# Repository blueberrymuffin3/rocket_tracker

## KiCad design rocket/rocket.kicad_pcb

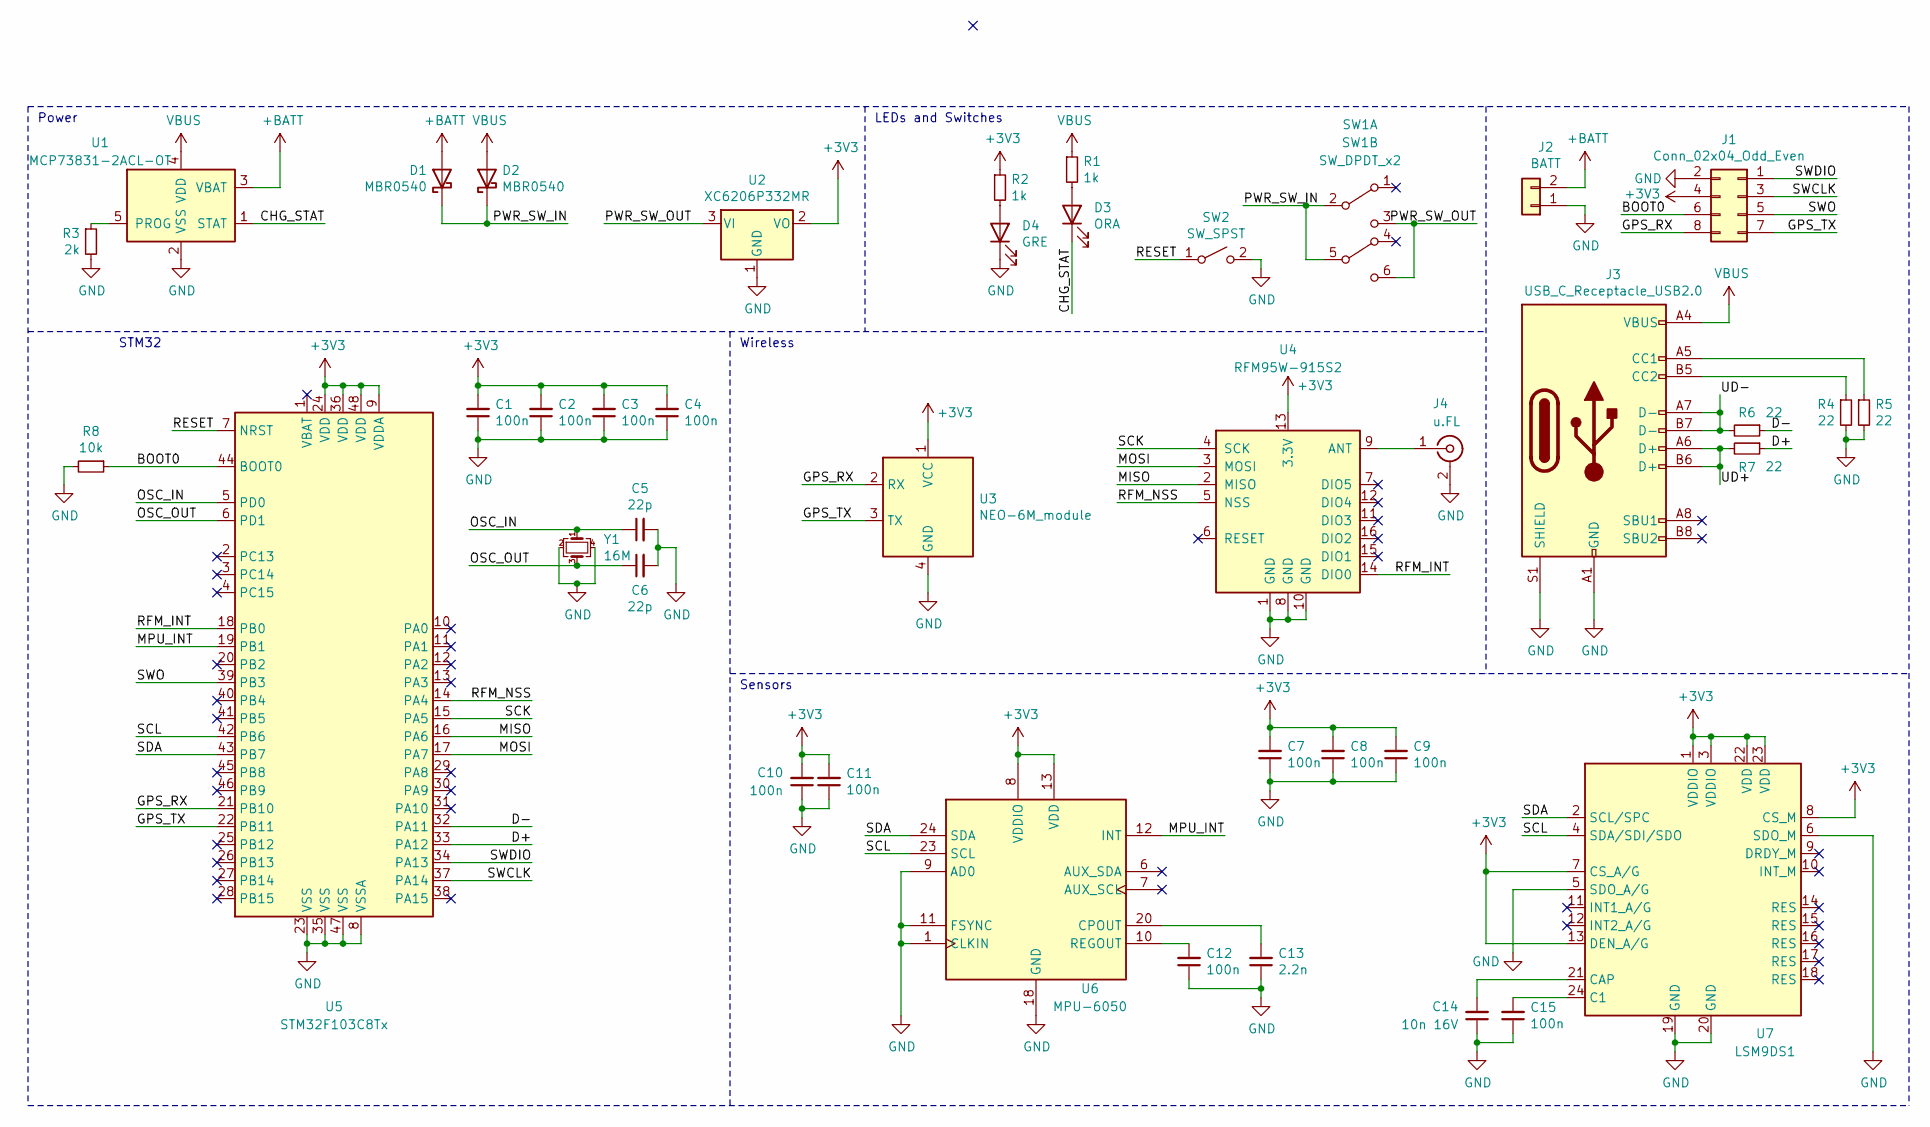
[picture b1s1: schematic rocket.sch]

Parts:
C1, C2, C3, C4, C7, C8, C9, C10, C11, C12, C15: 100n; C_0402_1005Metric; JLCPCB # C1525
C5, C6: 22p; C_0402_1005Metric; JLCPCB # C1555
C13: 2.2n; C_0402_1005Metric; JLCPCB # C1531
C14: 10n 16V; C_0402_1005Metric; JLCPCB # C15195
D1, D2: MBR0540; D_SOD-123; DIGIKEY # MBR0540TPMSCT-ND
D3: ORA; LED_0603_1608Metric; DIGIKEY # 160-1445-1-ND
D4: GRE; LED_0603_1608Metric; DIGIKEY # 160-1446-1-ND
J1: Conn_02x04_Odd_Even; PinSocket_2x04_P1.27mm_Horizontal_Straddle; DIGIKEY # 609-3753-ND, 609-3753-ND, 2057-RS1-04-G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
J2: BATT; JST_PH_S2B-PH-SM4-TB_1x02-1MP_P2.00mm_Horizontal; DIGIKEY # 455-1749-1-ND
J3: USB_C_Receptacle_USB2.0; GCT_USB4110-GF-A; DIGIKEY # 2073-USB4110-GF-A-1-ND
J4: u.FL; U.FL_Molex_MCRF_73412-0110_Vertical; DIGIKEY # A118077CT-ND
R1, R2: 1k; R_0402_1005Metric; JLCPCB # C11702
R3: 2k; R_0402_1005Metric; JLCPCB # C4109
R4, R5, R6, R7: 22; R_0402_1005Metric; JLCPCB # C25092
R8: 10k; R_0402_1005Metric; JLCPCB # C25744
SW1: SW_DPDT_x2; SW_DPDT_CK_JS202011JAQN; DIGIKEY # CKN10722CT-ND
SW2: SW_SPST; SW_Push_1P1T_KSS231; DIGIKEY # 401-1098-1-ND
U1: MCP73831-2ACL-OT; SOT-23-5; DIGIKEY # MCP73831T-2ACI/OTCT-ND
U2: XC6206P332MR; SOT-23; JLCPCB # C5446
U3: NEO-6M_module
U4: RFM95W-915S2; HOPERF_RFM9XW_SMD; DIGIKEY # RFM95W-915S2-ND
U5: STM32F103C8Tx; LQFP-48_7x7mm_P0.5mm; JLCPCB # C8734
U6: MPU-6050; InvenSense_QFN-24_4x4mm_P0.5mm; JLCPCB # C24112
U7: LSM9DS1; LGA-24L_3x3.5mm_P0.43mm_Handsolder; DIGIKEY # 497-14946-1-ND
Y1: 16M; Crystal_SMD_3225-4Pin_3.2x2.5mm; JLCPCB # C13738

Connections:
+3V3: C1.2, C2.2, C3.2, C4.2, C7.2, C8.2, C9.2, C10.2, C11.2, J1.4, R2.1, U2.2 (VO), U3.1 (VCC), U4.13 (3.3V), U5.9 (VDDA), U5.24 (VDD), U5.36 (VDD), U5.48 (VDD), U6.8 (VDDIO), U6.13 (VDD), U7.1 (VDDIO), U7.3 (VDDIO), U7.7 (CS_A/G), U7.8 (CS_M), U7.13 (DEN_A/G), U7.22 (VDD), U7.23 (VDD)
+BATT: D1.2 (A), J2.2, U1.3 (VBAT)
/BOOT0: J1.6, R8.1, U5.44 (BOOT0)
/CHG_STAT: D3.1 (K), U1.1 (STAT)
/D+: R7.1, U5.33 (PA12)
/D-: R6.1, U5.32 (PA11)
/GPS_RX: J1.8, U3.2 (RX), U5.21 (PB10)
/GPS_TX: J1.7, U3.3 (TX), U5.22 (PB11)
/MISO: U4.2 (MISO), U5.16 (PA6)
/MOSI: U4.3 (MOSI), U5.17 (PA7)
/MPU_INT: U5.19 (PB1), U6.12 (INT)
/OSC_IN: C5.1, U5.5 (PD0), Y1.1
/OSC_OUT: C6.1, U5.6 (PD1), Y1.3
/PWR_SW_IN: D1.1 (K), D2.1 (K), SW1.2 (B), SW1.5 (B)
/PWR_SW_OUT: SW1.3 (C), SW1.6 (C), U2.3 (VI)
/RESET: SW2.1 (A), U5.7 (NRST)
/RFM_INT: U4.14 (DIO0), U5.18 (PB0)
/RFM_NSS: U4.5 (NSS), U5.14 (PA4)
/SCK: U4.4 (SCK), U5.15 (PA5)
/SCL: U5.42 (PB6), U6.23 (SCL), U7.4 (SDA/SDI/SDO)
/SDA: U5.43 (PB7), U6.24 (SDA), U7.2 (SCL/SPC)
/SWCLK: J1.3, U5.37 (PA14)
/SWDIO: J1.1, U5.34 (PA13)
/SWO: J1.5, U5.39 (PB3)
/UD+: J3.A6 (D+), J3.B6 (D+), R7.2
/UD-: J3.A7 (D-), J3.B7 (D-), R6.2
GND: C1.1, C2.1, C3.1, C4.1, C5.2, C6.2, C7.1, C8.1, C9.1, C10.1, C11.1, C12.1, C13.1, C14.1, C15.1, D4.1 (K), J1.2, J2.1, J3.A1 (GND), J3.A12 (GND), J3.B1 (GND), J3.B12 (GND), J3.S1 (SHIELD), J4.2 (Ext), R3.2, R4.2, R5.2, R8.2, SW2.2 (B), U1.2 (VSS), U2.1 (GND), U3.4 (GND), U4.1 (GND), U4.8 (GND), U4.10 (GND), U5.8 (VSSA), U5.23 (VSS), U5.35 (VSS), U5.47 (VSS), U6.1 (CLKIN), U6.9 (AD0), U6.11 (FSYNC), U6.18 (GND), U7.5 (SDO_A/G), U7.6 (SDO_M), U7.19 (GND), U7.20 (GND), Y1.2, Y1.4
unnamed: C12.2, U6.10 (REGOUT)
unnamed: C13.2, U6.20 (CPOUT)
unnamed: C14.2, U7.21 (CAP)
unnamed: C15.2, U7.24 (C1)
unnamed: D3.2 (A), R1.2
unnamed: D4.2 (A), R2.2
unnamed: J3.A5 (CC1), R5.1
unnamed: J3.B5 (CC2), R4.1
unnamed: J4.1 (In), U4.9 (ANT)
unnamed: R3.1, U1.5 (PROG)
VBUS: D2.2 (A), J3.A4 (VBUS), J3.A9 (VBUS), J3.B4 (VBUS), J3.B9 (VBUS), R1.1, U1.4 (VDD)

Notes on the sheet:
Power
STM32
LEDs and Switches
Wireless
Sensors

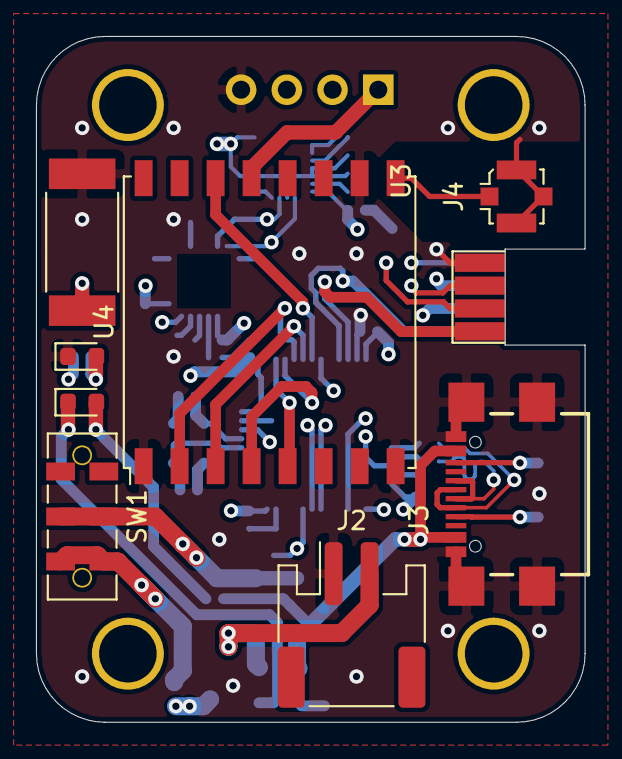
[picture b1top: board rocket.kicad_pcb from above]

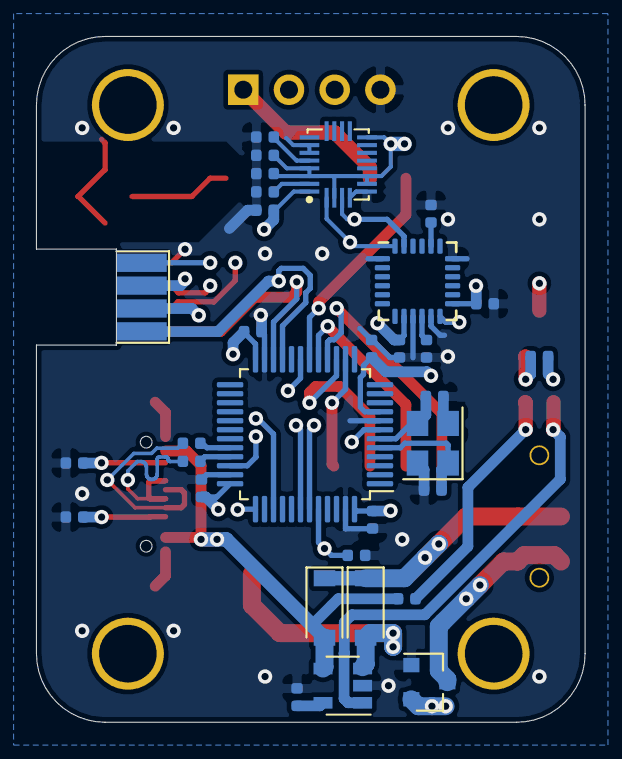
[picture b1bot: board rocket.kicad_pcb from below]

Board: 4 copper layers, 30.5 x 38.1 mm, 41 parts (32 on the bottom side), 38 nets.

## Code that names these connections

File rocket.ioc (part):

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PA6.Mode=Full_Duplex_Master
PA7.Mode=Full_Duplex_Master
PD1-OSC_OUT.Mode=HSE-External-Oscillator
Mcu.UserName=STM32F103C8Tx
PB10.Mode=Asynchronous
PA11.Mode=Device
PB0.GPIO_Label=RFM_INT
PD0-OSC_IN.Signal=RCC_OSC_IN
PB11.Signal=USART3_RX
RCC.SYSCLKSource=RCC_SYSCLKSOURCE_PLLCLK
PD1-OSC_OUT.Signal=RCC_OSC_OUT
PA13.Signal=SYS_JTMS-SWDIO
PA12.Signal=USB_DP
PB11.Mode=Asynchronous
PA4.Mode=NSS_Signal_Hard_Output
PB6.Signal=I2C1_SCL
PB6.Mode=I2C
PD0-OSC_IN.Mode=HSE-External-Oscillator
PB10.Signal=USART3_TX
PA5.Signal=SPI1_SCK
PB3.Mode=Trace_Asynchronous_SW
board=custom
PB0.GPIOParameters=GPIO_Label
PA14.Mode=Trace_Asynchronous_SW
PB1.GPIO_Label=MPU_INT
PB7.Signal=I2C1_SDA
PA13.Mode=Trace_Asynchronous_SW
Mcu.Name=STM32F103C(8-B)Tx
PB3.Signal=SYS_JTDO-TRACESWO
PA4.Signal=SPI1_NSS
RCC.SYSCLKFreq_VALUE=48000000
Mcu.Package=LQFP48
PB1.Signal=GPXTI1
PA6.Signal=SPI1_MISO
PA12.Mode=Device
PB7.Mode=I2C
PA11.Signal=USB_DM
PA14.Signal=SYS_JTCK-SWCLK
PB0.Signal=GPXTI0
PB1.GPIOParameters=GPIO_Label
PA5.Mode=Full_Duplex_Master
PA7.Signal=SPI1_MOSI

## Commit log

2020-06-24 Prototype v1
2020-06-24 Prototype v2
2020-06-28 Prototype v3
2020-06-28 STM32CubeMX file for the rocket
2020-06-28 Symbol, Footprint, and 3D libraries added
